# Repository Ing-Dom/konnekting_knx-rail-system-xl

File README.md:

# KNX Rail System XL

The KNX Rail System XL (KRS-XL) is a bunch of modular hard- and software for building DIY KNX devices in big DIN Rail Casings (6, 9 and 12 TE). It is designed for applications with a high number of channels. 

For more information please visit the [wiki](https://gitlab.com/knx-makerstuff/knx-rail-system-xl/-/wikis/home)

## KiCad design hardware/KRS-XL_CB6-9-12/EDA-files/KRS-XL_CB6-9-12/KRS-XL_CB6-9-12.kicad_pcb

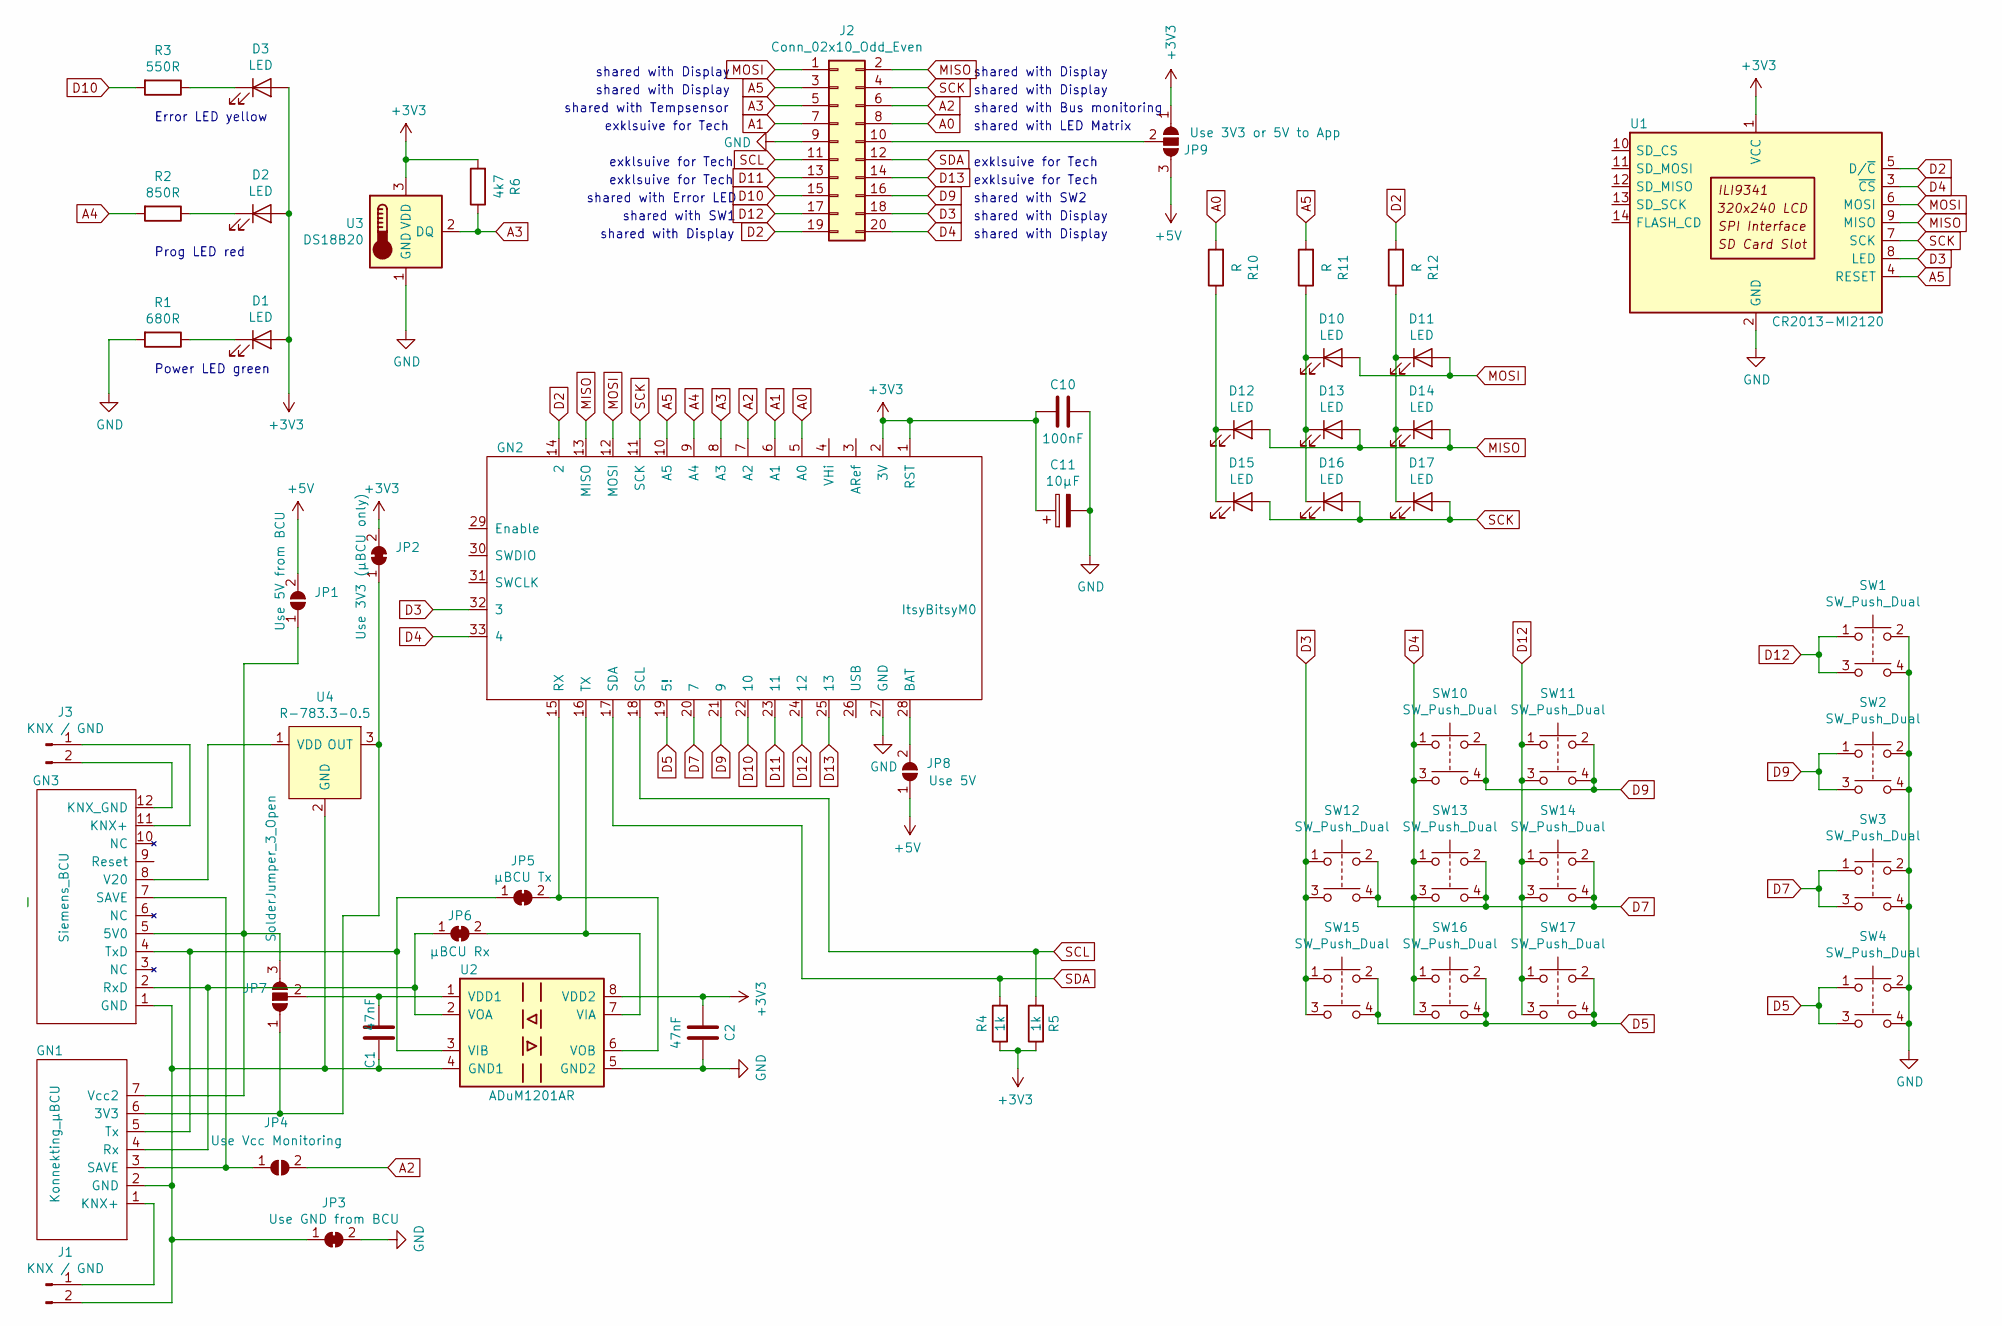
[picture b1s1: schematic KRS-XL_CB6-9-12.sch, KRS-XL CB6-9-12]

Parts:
C1, C2: 47nF; C_1206_3216Metric_Pad1.42x1.75mm_HandSolder
C10: 100nF; C_1206_3216Metric_Pad1.42x1.75mm_HandSolder
C11: 10µF; CP_Elec_5x5.3
D1, D2, D3, D10, D11, D12, D13, D14, D15, D16, D17: LED; LED_D3.0mm_Clear
GN1: Konnekting_µBCU; Konnekting_BCU
GN2: ItsyBitsyM0
GN3: Siemens_BCU; Siemens_UP117_12_flat
J1, J3: KNX / GND; PinHeader_1x02_P2.54mm_Vertical
J2: Conn_02x10_Odd_Even; IDC-Header_2x10_P2.54mm_Vertical
JP1: Use 5V from BCU; 3mm_solderjumper
JP2: Use 3V3 (µBCU only); 3mm_solderjumper
JP3: Use GND from BCU; 3mm_solderjumper
JP4: Use Vcc Monitoring; 3mm_solderjumper
JP5: µBCU Tx; 3mm_solderjumper
JP6: µBCU Rx; 3mm_solderjumper
JP7: SolderJumper_3_Open; SolderJumper-3_P1.3mm_Open_RoundedPad1.0x1.5mm
JP8: Use 5V; SolderJumper-2_P1.3mm_Open_RoundedPad1.0x1.5mm
JP9: Use 3V3 or 5V to App; SolderJumper-3_P1.3mm_Open_RoundedPad1.0x1.5mm
R1: 680R; R_1206_3216Metric_Pad1.42x1.75mm_HandSolder
R2: 850R; R_1206_3216Metric_Pad1.42x1.75mm_HandSolder
R3: 550R; R_1206_3216Metric_Pad1.42x1.75mm_HandSolder
R4, R5: 1k; R_1206_3216Metric_Pad1.42x1.75mm_HandSolder
R6: 4k7; R_1206_3216Metric_Pad1.42x1.75mm_HandSolder
R10, R11, R12: R; R_1206_3216Metric_Pad1.42x1.75mm_HandSolder
SW1, SW2, SW3, SW4, SW10, SW11, SW12, SW13, SW14, SW15, SW16, SW17: SW_Push_Dual; Switch_Tactile_SMD_6x6mm
U1: CR2013-MI2120; CR2013-MI2120_wo_holes
U2: ADuM1201AR; SOIC-8_3.9x4.9mm_P1.27mm
U3: DS18B20; TO-92_Inline
U4: R-783.3-0.5; SIP-3_P2.54mm_OR_4; MPN R-78E5.0-0.5; Digi-Key_PN 945-1648-5-ND

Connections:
+3V3: C2.2, C10.2, C11.1, D1.2 (A), D2.2 (A), D3.2 (A), GN2.1 (RST), GN2.2 (3V), JP2.2 (B), JP9.1 (A), R4.1, R5.1, R6.2, U1.1 (VCC), U2.8 (VDD2), U3.3 (VDD)
+5V: JP1.2 (B), JP8.1 (A), JP9.3 (B)
A0: GN2.5 (A0), J2.8, R10.2
A1: GN2.6 (A1), J2.7
A2: GN2.7 (A2), J2.6, JP4.2 (B)
A3: GN2.8 (A3), J2.5, R6.1, U3.2 (DQ)
A4: GN2.9 (A4), R2.2
A5: GN2.10 (A5), J2.3, R11.2, U1.4 (RESET)
D2: GN2.14 (2), J2.19, R12.2, U1.5 (D/~C)
D3: GN2.32 (3), J2.18, SW12.1, SW12.3, SW15.1, SW15.3, U1.8 (LED)
D4: GN2.33 (4), J2.20, SW10.1, SW10.3, SW13.1, SW13.3, SW16.1, SW16.3, U1.3 (~CS)
D5: GN2.19 (5!), SW4.1, SW4.3, SW15.2, SW15.4, SW16.2, SW16.4, SW17.2, SW17.4
D7: GN2.20 (7), SW3.1, SW3.3, SW12.2, SW12.4, SW13.2, SW13.4, SW14.2, SW14.4
D9: GN2.21 (9), J2.16, SW2.1, SW2.3, SW10.2, SW10.4, SW11.2, SW11.4
D10: GN2.22 (10), J2.15, R3.2
D11: GN2.23 (11), J2.13
D12: GN2.24 (12), J2.17, SW1.1, SW1.3, SW11.1, SW11.3, SW14.1, SW14.3, SW17.1, SW17.3
D13: GN2.25 (13), J2.14
GND: C2.1, C10.1, C11.2, GN2.27 (GND), J2.9, JP3.2 (B), R1.2, SW1.2, SW1.4, SW2.2, SW2.4, SW3.2, SW3.4, SW4.2, SW4.4, U1.2 (GND), U2.5 (GND2), U3.1 (GND)
MISO: D12.2 (A), D13.2 (A), D14.2 (A), GN2.13 (MISO), J2.2, U1.9 (MISO)
MOSI: D10.2 (A), D11.2 (A), GN2.12 (MOSI), J2.1, U1.6 (MOSI)
unnamed: C1.1, JP7.2 (C), U2.1 (VDD1)
unnamed: C1.2, GN1.2 (GND), GN3.1 (GND), J1.2, JP3.1 (A), U2.4 (GND1), U4.2 (GND)
unnamed: D1.1 (K), R1.1
unnamed: D2.1 (K), R2.1
unnamed: D3.1 (K), R3.1
unnamed: D10.1 (K), D13.1 (K), D16.1 (K), R11.1
unnamed: D11.1 (K), D14.1 (K), D17.1 (K), R12.1
unnamed: D12.1 (K), D15.1 (K), R10.1
unnamed: GN1.1 (KNX+), J1.1
unnamed: GN1.3 (SAVE), GN3.7 (SAVE), JP4.1 (A)
unnamed: GN1.4 (Rx), GN3.2 (RxD), JP6.1 (A), U2.2 (VOA)
unnamed: GN1.5 (Tx), GN3.4 (TxD), JP5.1 (A), U2.3 (VIB)
unnamed: GN1.6 (3V3), JP2.1 (A), JP7.1 (A), U4.3 (OUT)
unnamed: GN1.7 (Vcc2), GN3.5 (5V0), JP1.1 (A), JP7.3 (B)
unnamed: GN2.15 (RX), JP5.2 (B), U2.6 (VOB)
unnamed: GN2.16 (TX), JP6.2 (B), U2.7 (VIA)
unnamed: GN2.28 (BAT), JP8.2 (B)
unnamed: GN3.8 (V20), U4.1 (VDD)
unnamed: GN3.11 (KNX+), J3.1
unnamed: GN3.12 (KNX_GND), J3.2
unnamed: J2.10, JP9.2 (C)
SCK: D15.2 (A), D16.2 (A), D17.2 (A), GN2.11 (SCK), J2.4, U1.7 (SCK)
SCL: GN2.18 (SCL), J2.11, R5.2
SDA: GN2.17 (SDA), J2.12, R4.2

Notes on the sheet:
Power LED green
Prog LED red
Error LED yellow
shared with Display
shared with SW1
shared with SW2
exklsuive for Tech
shared with Error LED
shared with Tempsensor
shared with Bus monitoring
shared with LED Matrix

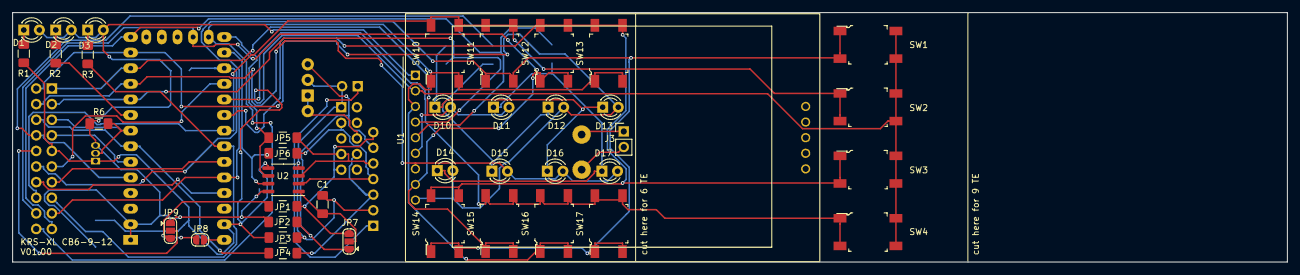
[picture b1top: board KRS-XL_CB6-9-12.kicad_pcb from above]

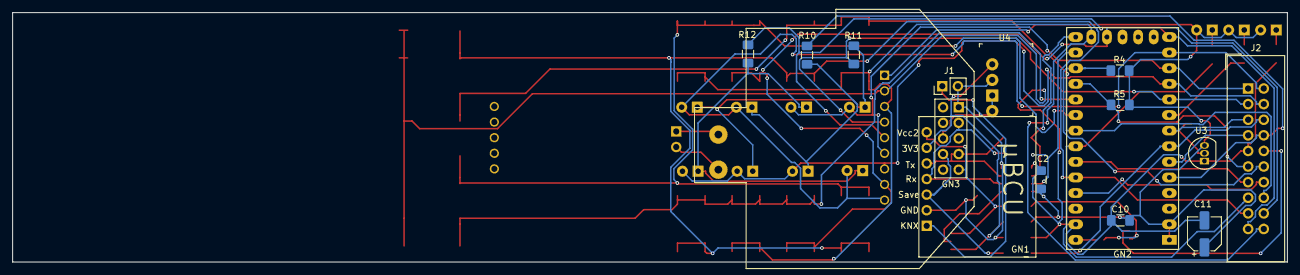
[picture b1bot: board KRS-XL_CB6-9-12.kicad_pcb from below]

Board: 2 copper layers, 207.5 x 40.6 mm, 55 parts (15 on the bottom side), 45 nets.

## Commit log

2021-02-05 KRS-XL_CB6-9-12_V01.00 from sirsydom/konnekting_common
2021-02-05 worked on V01.01 - RST of ItsyBitsy disconnected from 3v3
2021-02-05 Add LICENSE
2021-02-09 datasheets
2021-02-11 added PCB render, improved BOM
2022-01-22 V01.01
